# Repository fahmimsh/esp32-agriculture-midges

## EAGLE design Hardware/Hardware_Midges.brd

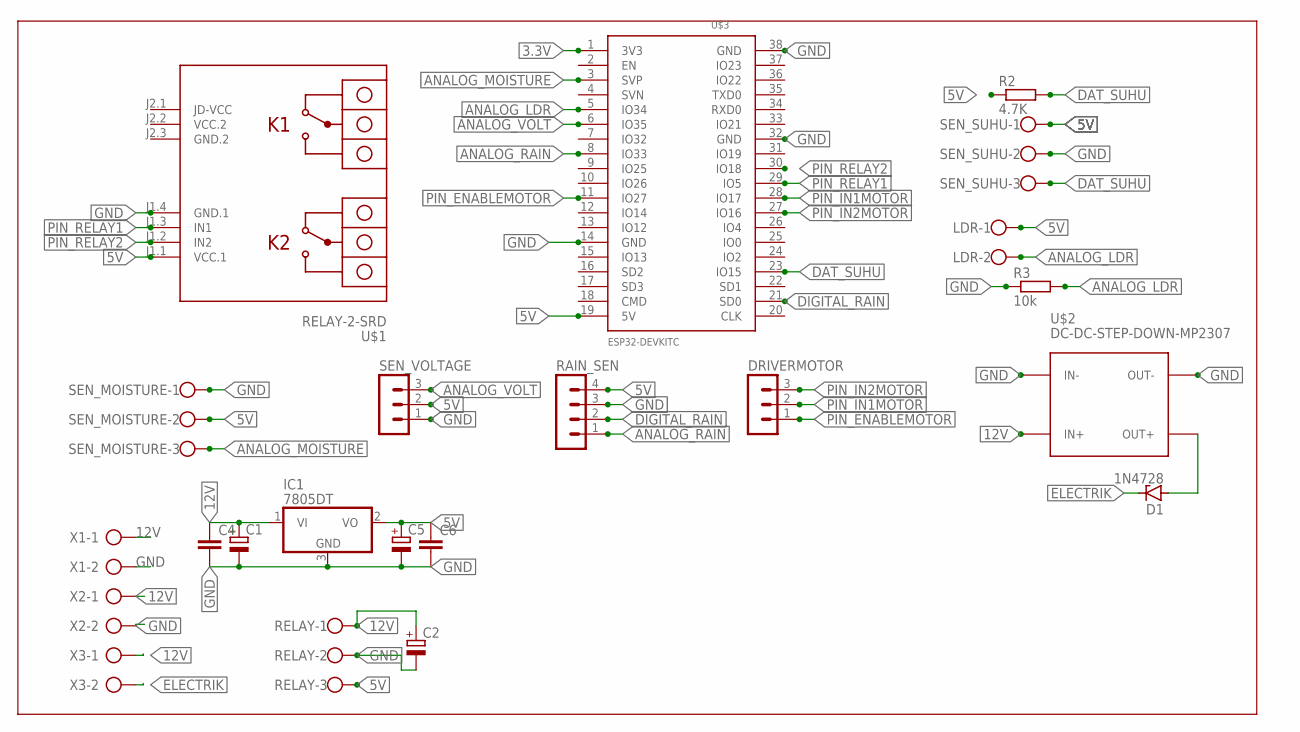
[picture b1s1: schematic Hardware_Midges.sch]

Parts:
C1, C5: CPOL-EUE5-6; E5-6
C2: CPOL-EUE5-10.5; E5-10,5
C4, C6: C-EU050-025X075; C050-025X075
D1: 1N4728; DO41Z10
DRIVERMOTOR: MA03-1
IC1: 7805DT; TO252
LDR: W237-102
R2: 4.7K; 0207/10
R3: 10k; 0207/10
RAIN_SEN: MA04-1
RELAY: W237-103
SEN_MOISTURE: W237-103
SEN_SUHU: W237-103
SEN_VOLTAGE: MA03-1
U$1: RELAY-2-SRD
U$2: DC-DC-STEP-DOWN-MP2307
U$3: ESP32DEVKITC; ESP32-DEVKITC
X1, X2, X3: AK500/2-H

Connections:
3.3V: U$3.1 (3V3)
5V: C5.+, C6.1, IC1.2 (VO), LDR.1, R2.1, RAIN_SEN.4, RELAY.3, SEN_MOISTURE.2, SEN_SUHU.1, SEN_VOLTAGE.2, U$1.J1.1 (VCC.1), U$3.19 (5V)
12V: C1.+, C2.+, C4.1, IC1.1 (VI), RELAY.1, U$2.IN+, X1.1, X2.1, X3.1
ANALOG_LDR: LDR.2, R3.2, U$3.5 (IO34)
ANALOG_MOISTURE: SEN_MOISTURE.3, U$3.3 (SVP)
ANALOG_RAIN: RAIN_SEN.1, U$3.8 (IO33)
ANALOG_VOLT: SEN_VOLTAGE.3, U$3.6 (IO35)
DAT_SUHU: R2.2, SEN_SUHU.3, U$3.23 (IO15)
DIGITAL_RAIN: RAIN_SEN.2, U$3.21 (SD0)
ELECTRIK: D1.C, X3.2
GND: C1.-, C2.-, C4.2, C5.-, C6.2, IC1.3 (GND), R3.1, RAIN_SEN.3, RELAY.2, SEN_MOISTURE.1, SEN_SUHU.2, SEN_VOLTAGE.1, U$1.J1.4 (GND.1), U$2.IN-, U$2.OUT-, U$3.14 (GND), U$3.32 (GND), U$3.38 (GND), X1.2, X2.2
GND.2: U$1.J2.3 (GND.2)
unnamed: D1.A, U$2.OUT+
PIN_ENABLEMOTOR: DRIVERMOTOR.1, U$3.11 (IO27)
PIN_IN1MOTOR: DRIVERMOTOR.2, U$3.28 (IO17)
PIN_IN2MOTOR: DRIVERMOTOR.3, U$3.27 (IO16)
PIN_RELAY1: U$1.J1.3 (IN1), U$3.29 (IO5)
PIN_RELAY2: U$1.J1.2 (IN2), U$3.30 (IO18)
VCC.2: U$1.J2.2 (VCC.2)

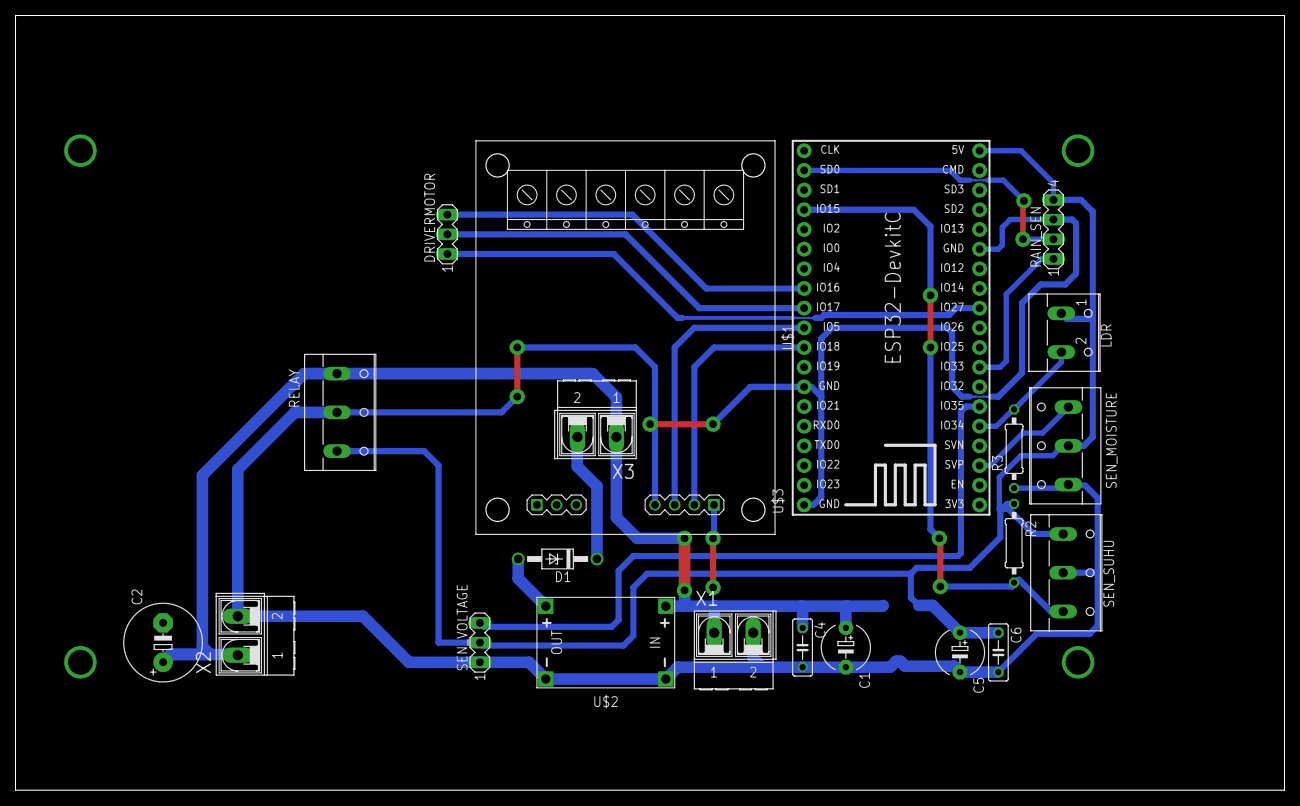
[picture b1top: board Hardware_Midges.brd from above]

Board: 2 copper layers, 163.8 x 100.0 mm, 22 parts (1 on the bottom side), 16 nets.

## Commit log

2020-11-17 agriculture

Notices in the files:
parts and their libraries:
diy-modules: Released under the Creative Commons Attribution 4.0 International License: http://creativecommons.org/licenses/by/4.0
